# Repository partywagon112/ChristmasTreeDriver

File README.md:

# Christmas Tree Driver
This really should get renamed, but the idea is to create a Matter based H-Bridge driver for my Home Assistant to control my Christmas tree lights at the end of the year.

Very much an in-progress effort...

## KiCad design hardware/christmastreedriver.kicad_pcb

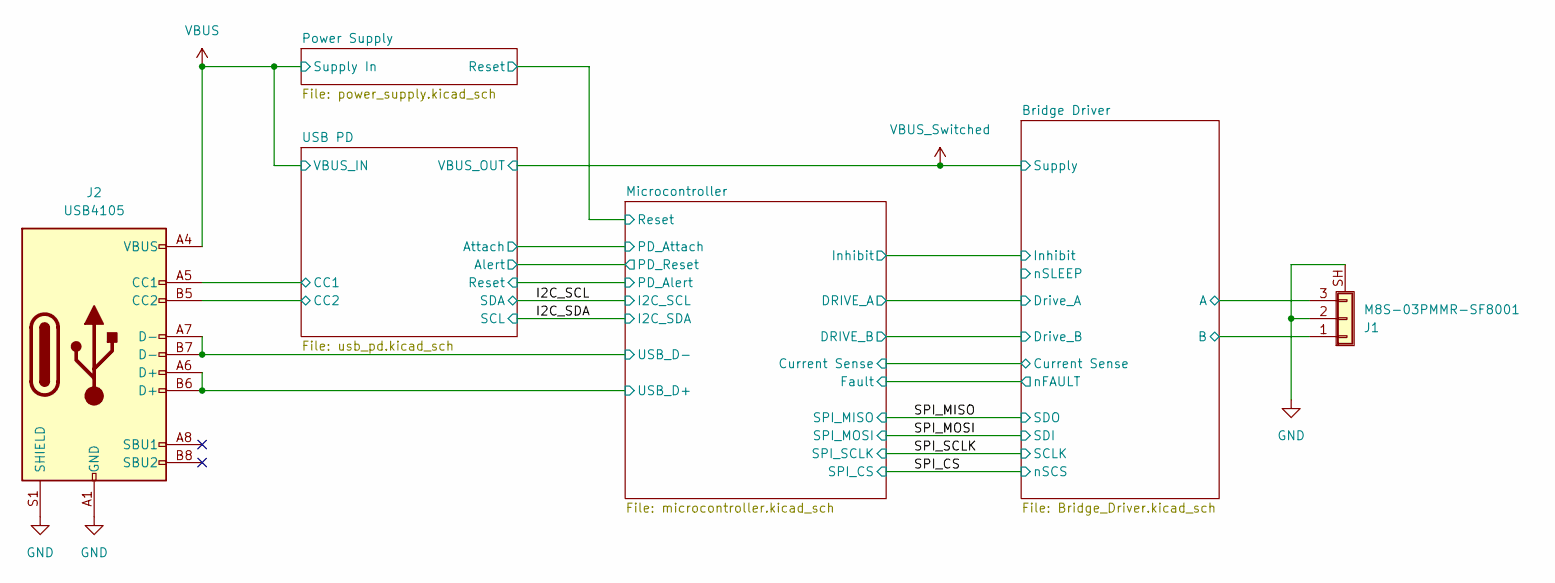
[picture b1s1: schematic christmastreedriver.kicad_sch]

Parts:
J1: M8S-03PMMR-SF8001; Amphenol_M8S-03PMMR-SF8001; MPN M8S-03PMMR-SF8001
J2: USB4105; USB_C_Receptacle_GCT_USB4105-xx-A_16P_TopMnt_Horizontal; MPN USB4105-GF-A

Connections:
/Bridge Driver/A: J1.3; also elsewhere on the board
/Bridge Driver/B: J1.1; also elsewhere on the board
/Microcontroller/USB_D+: J2.A6 (D+), J2.B6 (D+); also elsewhere on the board
/Microcontroller/USB_D-: J2.A7 (D-), J2.B7 (D-); also elsewhere on the board
/USB PD/CC1: J2.A5 (CC1); also elsewhere on the board
/USB PD/CC2: J2.B5 (CC2); also elsewhere on the board
GND: J1.2, J1.SH (Shield), J2.A1 (GND), J2.A12 (GND), J2.B1 (GND), J2.B12 (GND), J2.S1 (SHIELD); also elsewhere on the board
VBUS: J2.A4 (VBUS), J2.A9 (VBUS), J2.B4 (VBUS), J2.B9 (VBUS); also elsewhere on the board

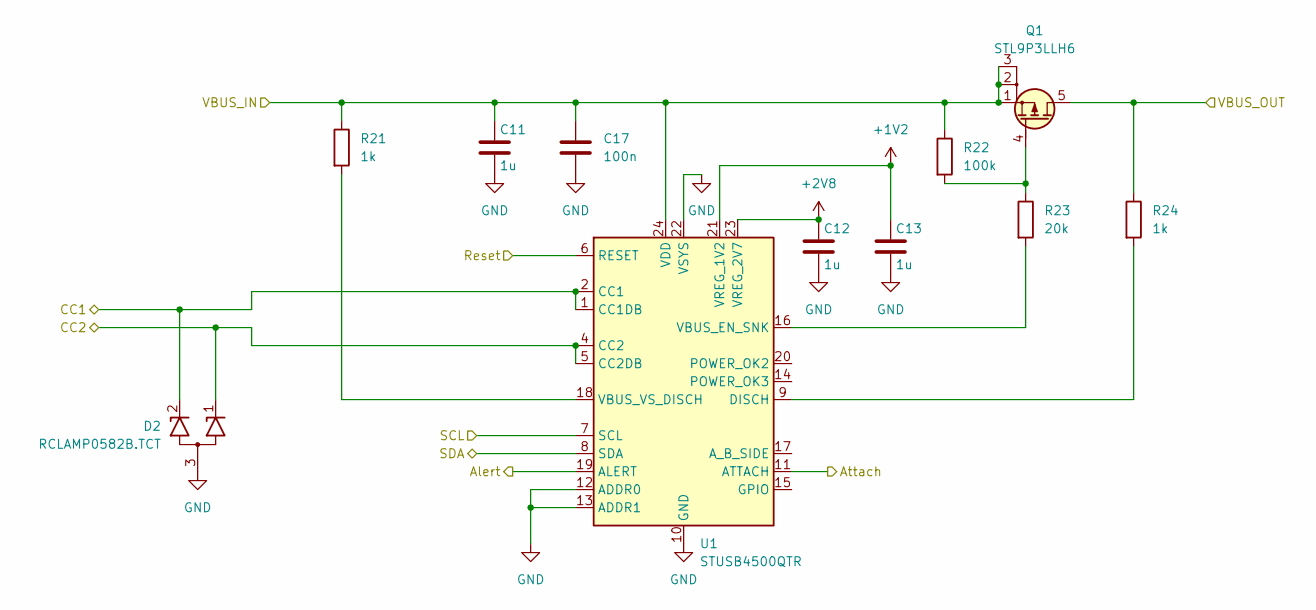
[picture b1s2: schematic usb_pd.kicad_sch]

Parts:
C11, C12, C13: 1u; C_0603_1608Metric; MPN GRT188R61H105KE13D
C17: 100n; C_0402_1005Metric; MPN GCM155R71H104KE02J
D2: RCLAMP0582B.TCT; SOT-416; MPN RCLAMP0582B.TCT
Q1: STL9P3LLH6; ST_PowerFlat-8; MPN STL9P3LLH6
R21, R24: 1k; R_0603_1608Metric; MPN CR0603AFX-1001ELF
R22: 100k; R_0402_1005Metric; MPN ERJ-2RKF1003X
R23: 20k; R_0402_1005Metric; MPN ERJ-2RKF2002X
U1: STUSB4500QTR; QFN-24-1EP_4x4mm_P0.5mm_EP2.7x2.7mm_ThermalVias; MPN STUSB4500QTR

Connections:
+1V2: C13.1, U1.21 (VREG_1V2)
+2V8: C12.1, U1.23 (VREG_2V7)
/I2C_SCL: U1.8 (SDA); also elsewhere on the board
/I2C_SDA: U1.7 (SCL); also elsewhere on the board
/Microcontroller/PD_Alert: U1.6 (RESET); also elsewhere on the board
/Microcontroller/PD_Attach: U1.11 (ATTACH); also elsewhere on the board
/Microcontroller/PD_Reset: U1.19 (ALERT); also elsewhere on the board
/USB PD/CC1: D2.2 (K2), U1.1 (CC1DB), U1.2 (CC1); also elsewhere on the board
/USB PD/CC2: D2.1 (K1), U1.4 (CC2), U1.5 (CC2DB); also elsewhere on the board
GND: C11.2, C12.2, C13.2, C17.2, D2.3 (A), U1.10 (GND), U1.12 (ADDR0), U1.13 (ADDR1), U1.22 (VSYS), U1.25 (GND); also elsewhere on the board
unnamed: Q1.4 (G), R22.2, R23.1
unnamed: R24.2, U1.9 (DISCH)
unnamed: R23.2, U1.16 (VBUS_EN_SNK)
unnamed: R21.2, U1.18 (VBUS_VS_DISCH)
VBUS: C11.1, C17.1, Q1.1 (S), Q1.2 (S), Q1.3 (S), R21.1, R22.1, U1.24 (VDD); also elsewhere on the board
VBUS_Switched: Q1.5 (D), R24.1; also elsewhere on the board

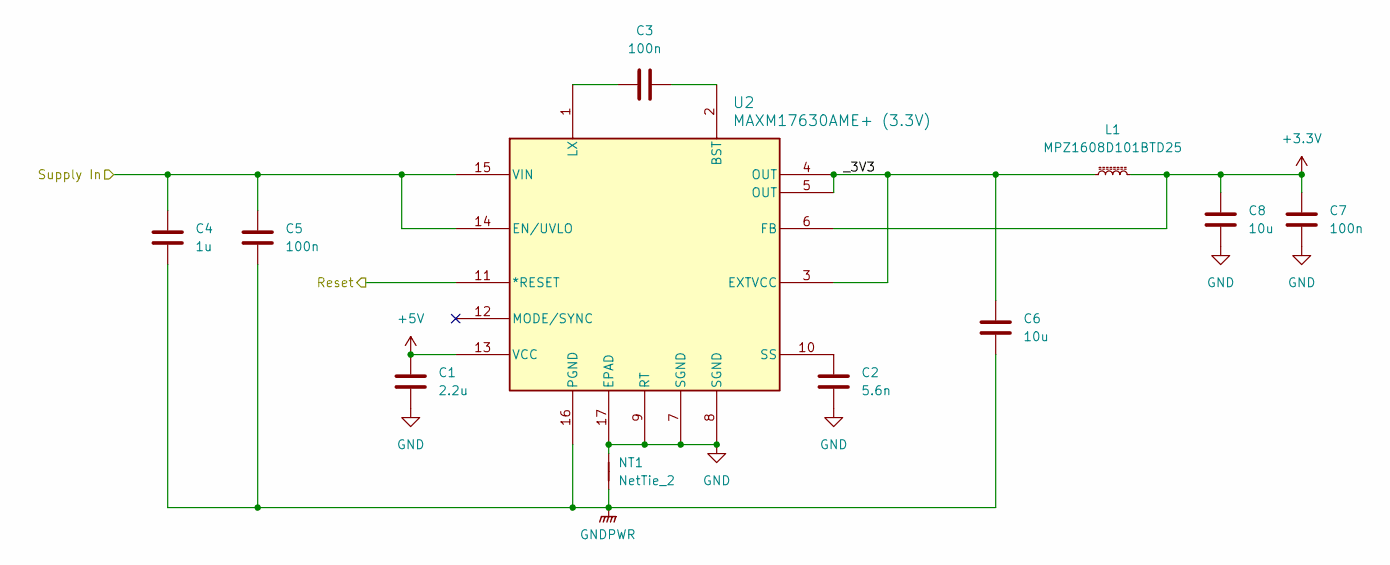
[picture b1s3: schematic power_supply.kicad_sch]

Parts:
C1: 2.2u; C_0603_1608Metric; MPN GRT188R61H225KE13D
C2: 5.6n; C_0402_1005Metric; MPN GCM155R71H562KA55D
C3, C5, C7: 100n; C_0402_1005Metric; MPN GCM155R71H104KE02J
C4: 1u; C_0603_1608Metric; MPN GRT188R61H105KE13D
C6, C8: 10u; C_0805_2012Metric; MPN GCM21BR70J106KE22L
L1: MPZ1608D101BTD25; L_0603_1608Metric; MPN MPZ1608D101BTD25
NT1: NetTie_2; NetTie-2_SMD_Pad0.5mm
U2: MAXM17630AME+ (3.3V); 16-eMGA (3x3); MPN MAXM17630AME+T

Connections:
+3.3V: C7.1, C8.1, L1.2, U2.6 (FB); also elsewhere on the board
+5V: C1.1, U2.13 (VCC); also elsewhere on the board
/Microcontroller/Reset: U2.11 (*RESET); also elsewhere on the board
/Power Supply/_3V3: C6.1, L1.1, U2.3 (EXTVCC), U2.4 (OUT), U2.5 (OUT)
GND: C1.2, C2.2, C7.2, C8.2, NT1.2, U2.7 (SGND), U2.8 (SGND), U2.9 (RT), U2.17 (EPAD); also elsewhere on the board
GNDPWR: C4.2, C5.2, C6.2, NT1.1, U2.16 (PGND)
unnamed: C3.2, U2.2 (BST)
unnamed: C3.1, U2.1 (LX)
unnamed: C2.1, U2.10 (SS)
VBUS: C4.1, C5.1, U2.14 (EN/UVLO), U2.15 (VIN); also elsewhere on the board

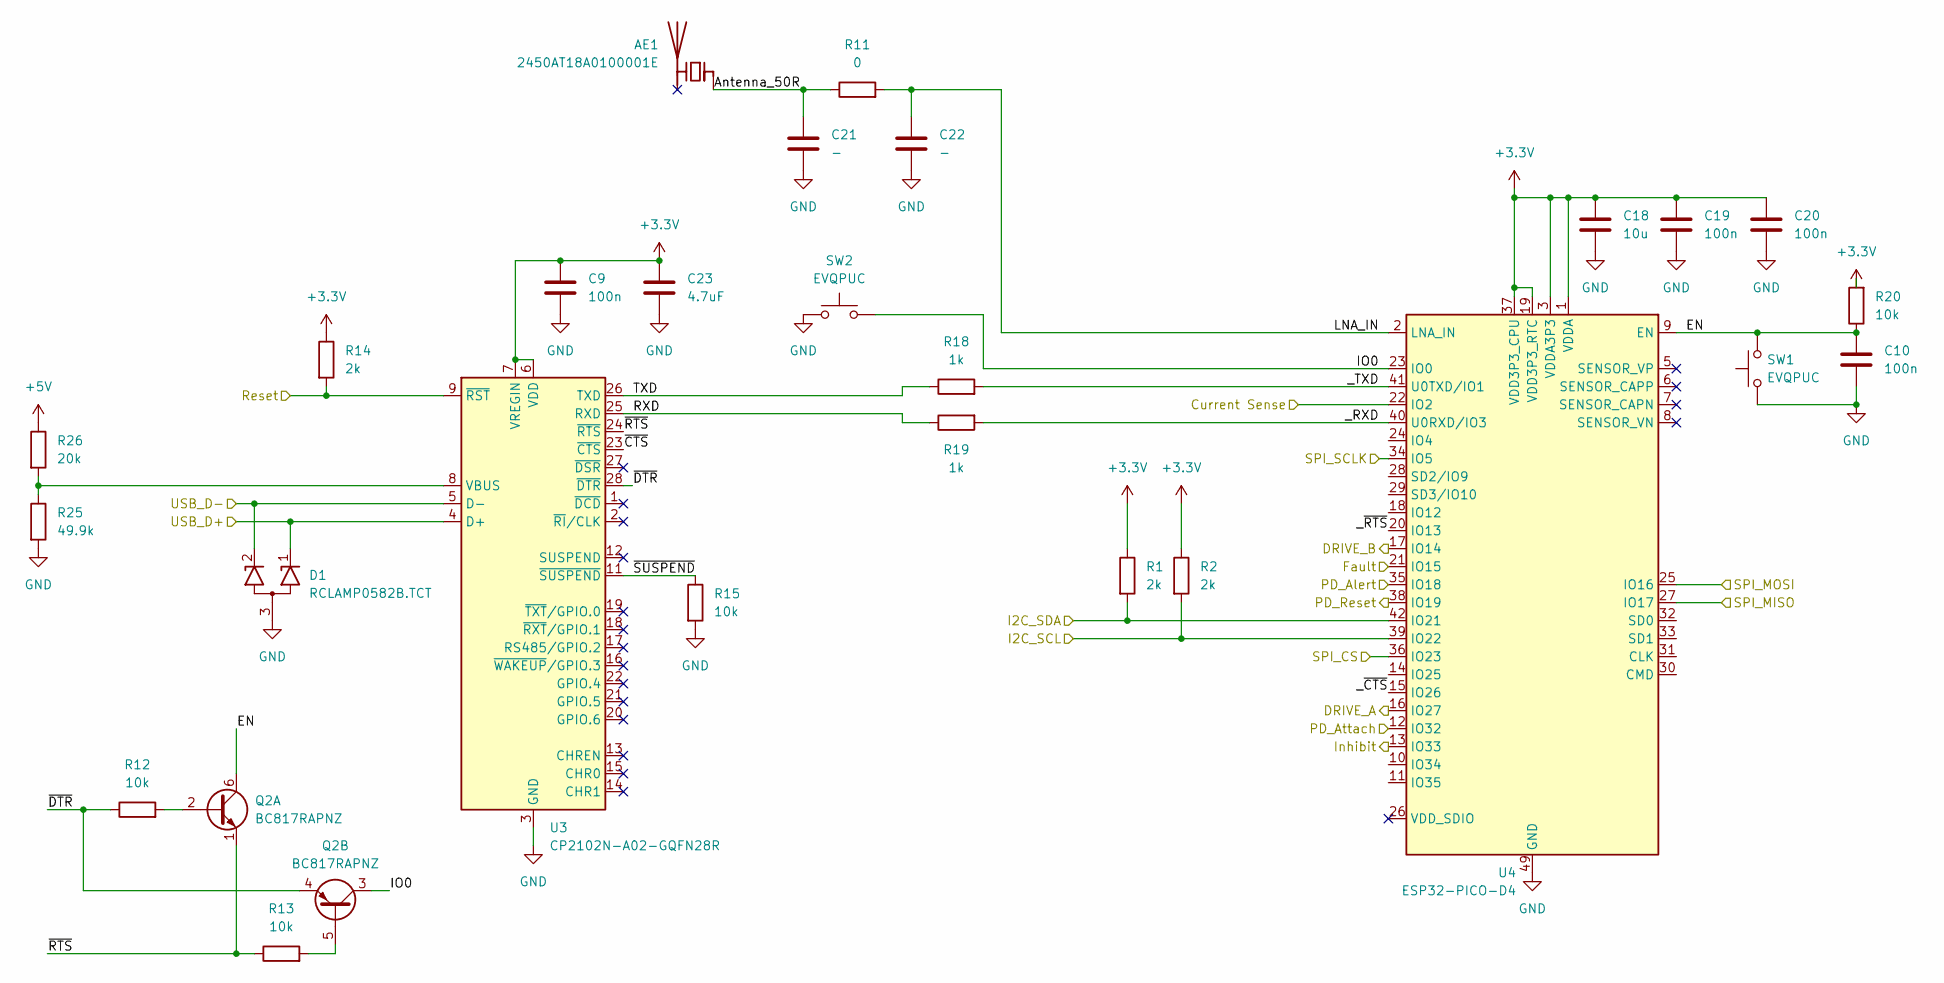
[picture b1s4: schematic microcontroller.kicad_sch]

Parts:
AE1: 2450AT18A0100001E; Johanson_2450AT18x100; MPN 2450AT18A0100001E
C9, C10, C19, C20: 100n; C_0402_1005Metric; MPN GCM155R71H104KE02J
C18: 10u; C_0805_2012Metric; MPN GCM21BR70J106KE22L
C21, C22: -; C_0402_1005Metric; Part-DB Footprint 0402
C23: 4.7uF; C_0805_2012Metric; MPN GCM21BC71A475KA73L
D1: RCLAMP0582B.TCT; SOT-416; MPN RCLAMP0582B.TCT
Q2: BC817RAPNZ; DFN1412-6; MPN BC817RAPNZ
R1, R2, R14: 2k; R_0402_1005Metric; MPN CR0402AFX-2001GAS
R11: 0; R_0402_1005Metric; MPN CR0402AJ/-000GLF
R12, R13, R15, R20: 10k; R_0402_1005Metric; MPN CR0402AFX-1002GAS
R18, R19: 1k; R_0402_1005Metric; MPN CR0402AFX-1001GAS
R25: 49.9k; R_0402_1005Metric; MPN CR0402AFX-4992GAS
R26: 20k; R_0402_1005Metric; MPN ERJ-2RKF2002X
SW1, SW2: EVQPUC; Panasonic_EVQPUL_EVQPUC; MPN EVQ-PUC02K
U3: CP2102N-A02-GQFN28R; QFN-28-1EP_5x5mm_P0.5mm_EP3.35x3.35mm_ThermalVias; MPN CP2102N-A02-GQFN28R
U4: ESP32-PICO-D4; QFN-48-1EP_7x7mm_P0.5mm_EP5.3x5.3mm_ThermalVias; MPN ESP32-PICO-D4

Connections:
+3.3V: C9.1, C18.1, C19.1, C20.1, C23.1, R1.1, R2.1, R14.1, R20.2, U3.6 (VDD), U3.7 (VREGIN), U4.1 (VDDA), U4.3 (VDDA3P3), U4.4 (VDDA3P3), U4.19 (VDD3P3_RTC), U4.37 (VDD3P3_CPU), U4.43 (VDDA), U4.46 (VDDA); also elsewhere on the board
+5V: R26.1; also elsewhere on the board
/Bridge Driver/Current Sense: U4.22 (IO2); also elsewhere on the board
/Bridge Driver/_DRVOFF: U4.13 (IO33); also elsewhere on the board
/Bridge Driver/_EN/IN1: U4.16 (IO27); also elsewhere on the board
/Bridge Driver/_PH/IN2: U4.17 (IO14); also elsewhere on the board
/Bridge Driver/nFAULT: U4.21 (IO15); also elsewhere on the board
/I2C_SCL: R2.2, U4.39 (IO22); also elsewhere on the board
/I2C_SDA: R1.2, U4.42 (IO21); also elsewhere on the board
/Microcontroller/Antenna_50R: AE1.1 (FEED), C21.1, R11.1
/Microcontroller/EN: C10.1, Q2.6 (C1), R20.1, SW1.2, U4.9 (EN)
/Microcontroller/IO0: Q2.3 (C2), SW2.2, U4.23 (IO0)
/Microcontroller/LNA_IN: C22.1, R11.2, U4.2 (LNA_IN)
/Microcontroller/PD_Alert: U4.35 (IO18); also elsewhere on the board
/Microcontroller/PD_Attach: U4.12 (IO32); also elsewhere on the board
/Microcontroller/PD_Reset: U4.38 (IO19); also elsewhere on the board
/Microcontroller/RXD: R19.1, U3.25 (RXD)
/Microcontroller/Reset: R14.2, U3.9 (~RST); also elsewhere on the board
/Microcontroller/TXD: R18.1, U3.26 (TXD)
/Microcontroller/USB_D+: D1.1 (K1), U3.4 (D+); also elsewhere on the board
/Microcontroller/USB_D-: D1.2 (K2), U3.5 (D-); also elsewhere on the board
/Microcontroller/_RXD: R19.2, U4.40 (U0RXD/IO3)
/Microcontroller/_TXD: R18.2, U4.41 (U0TXD/IO1)
/Microcontroller/_~CTS: U4.15 (IO26)
/Microcontroller/_~RTS: U4.20 (IO13)
/Microcontroller/~CTS: U3.23 (~CTS)
/Microcontroller/~DTR: Q2.4 (E2), R12.1, U3.28 (~DTR)
/Microcontroller/~RTS: Q2.1 (E1), R13.1, U3.24 (~RTS)
/Microcontroller/~SUSPEND: R15.1, U3.11 (~SUSPEND)
/SPI_CS: U4.36 (IO23); also elsewhere on the board
/SPI_MISO: U4.27 (IO17); also elsewhere on the board
/SPI_MOSI: U4.25 (IO16); also elsewhere on the board
/SPI_SCLK: U4.34 (IO5); also elsewhere on the board
GND: AE1.2 (PCB_Trace), C9.2, C10.2, C18.2, C19.2, C20.2, C21.2, C22.2, C23.2, D1.3 (A), R15.2, R25.2, SW1.1, SW2.1, U3.3 (GND), U3.29 (GND), U4.49 (GND); also elsewhere on the board
unnamed: Q2.2 (B1), R12.2
unnamed: Q2.5 (B2), R13.2
unnamed: R25.1, R26.2, U3.8 (VBUS)

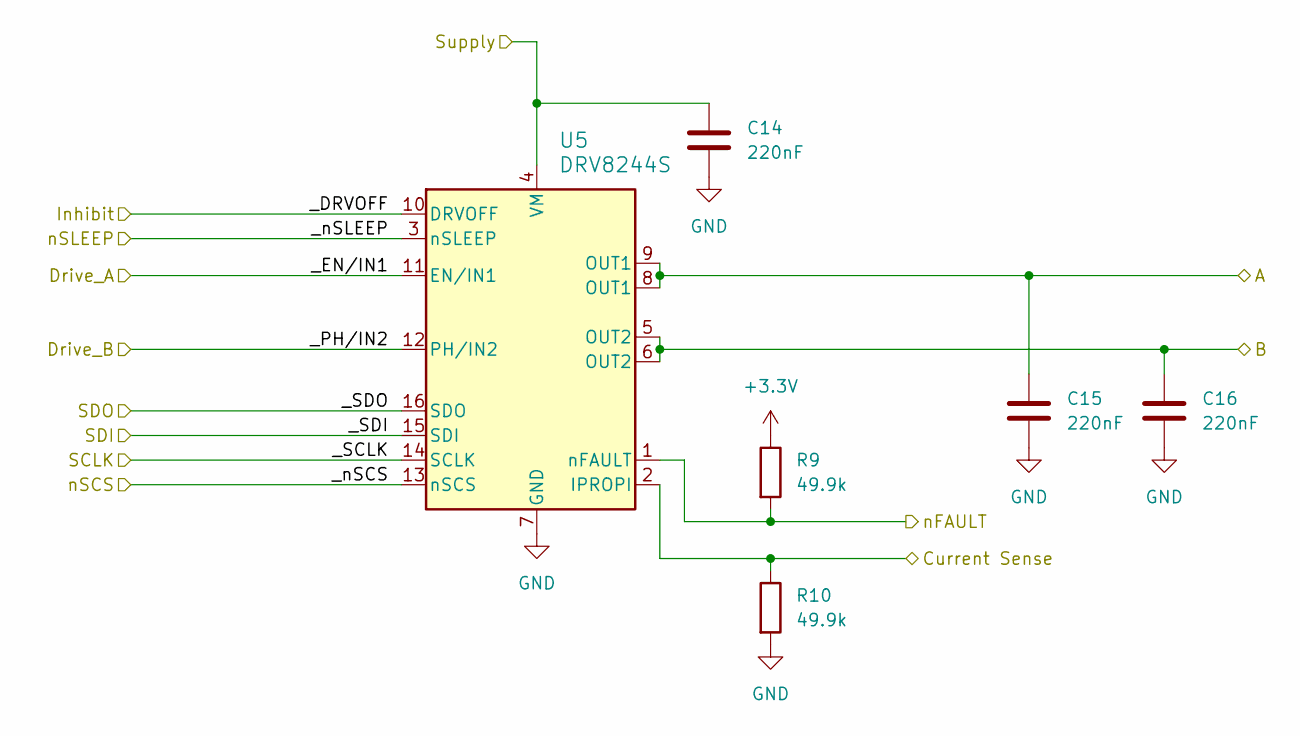
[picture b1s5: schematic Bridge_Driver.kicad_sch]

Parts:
C14, C15, C16: 220nF; C_0603_1608Metric; MPN GCM188R71H224KA64D
R9, R10: 49.9k; R_0402_1005Metric; MPN CR0402AFX-4992GAS
U5: DRV8244S; VQFN-16_RYJ_TEX; MPN DRV8244SQRYJRQ1

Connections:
+3.3V: R9.1; also elsewhere on the board
/Bridge Driver/A: C15.1, U5.8 (OUT1), U5.9 (OUT1); also elsewhere on the board
/Bridge Driver/B: C16.1, U5.5 (OUT2), U5.6 (OUT2); also elsewhere on the board
/Bridge Driver/Current Sense: R10.1, U5.2 (IPROPI); also elsewhere on the board
/Bridge Driver/_DRVOFF: U5.10 (DRVOFF); also elsewhere on the board
/Bridge Driver/_EN/IN1: U5.11 (EN/IN1); also elsewhere on the board
/Bridge Driver/_PH/IN2: U5.12 (PH/IN2); also elsewhere on the board
/Bridge Driver/_nSLEEP: U5.3 (nSLEEP)
/Bridge Driver/nFAULT: R9.2, U5.1 (nFAULT); also elsewhere on the board
/SPI_CS: U5.13 (nSCS); also elsewhere on the board
/SPI_MISO: U5.16 (SDO); also elsewhere on the board
/SPI_MOSI: U5.15 (SDI); also elsewhere on the board
/SPI_SCLK: U5.14 (SCLK); also elsewhere on the board
GND: C14.2, C15.2, C16.2, R10.2, U5.7 (GND); also elsewhere on the board
VBUS_Switched: C14.1, U5.4 (VM); also elsewhere on the board

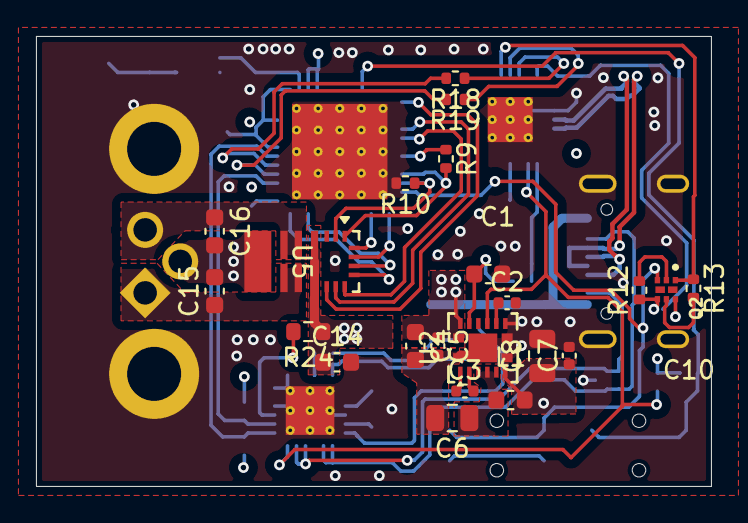
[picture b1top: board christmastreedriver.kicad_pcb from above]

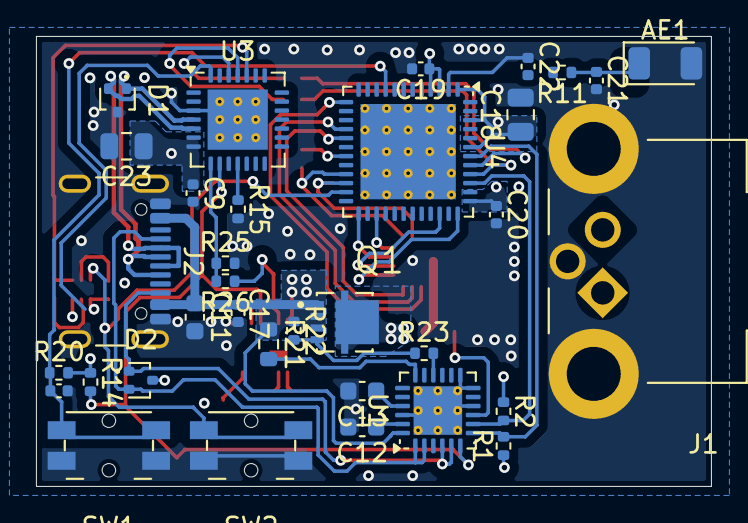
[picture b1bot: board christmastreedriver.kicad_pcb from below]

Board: 4 copper layers, 37.5 x 25.0 mm, 57 parts (34 on the bottom side), 51 nets.

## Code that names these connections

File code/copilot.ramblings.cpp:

#include <Wire.h>
#include <SPI.h>

// Define SPI pins
const int SPI_MISO = 17; // MISO (Master In Slave Out)
const int SPI_MOSI = 16; // MOSI (Master Out Slave In)
const int SPI_SCK = 5;   // SCK (Serial Clock)
const int SPI_CS = 23;   // CS (Chip Select)

// Define I2C pins
const int I2C_SDA = 21; // SDA (Serial Data)
const int I2C_SCL = 22; // SCL (Serial Clock)

void setup() {
  // Initialize SPI
  SPI.begin();
  // SPI.beginTransaction(SPISettings(1000000, MSBFIRST, SPI_MODE0));
  pinMode(SPI_CS, OUTPUT);

  // Initialize I2C
  Wire.begin(I2C_SDA, I2C_SCL);

  // Other setup code
}

void loop() {
  // Your SPI and I2C communication code here
}

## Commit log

2024-04-28 Added ignore
2024-04-28 Added ref image
2024-05-15 Generated first bom
2024-08-11 updated .gitignore
2024-08-11 Flipped some stuff
2024-08-11 Added code and matter repo
